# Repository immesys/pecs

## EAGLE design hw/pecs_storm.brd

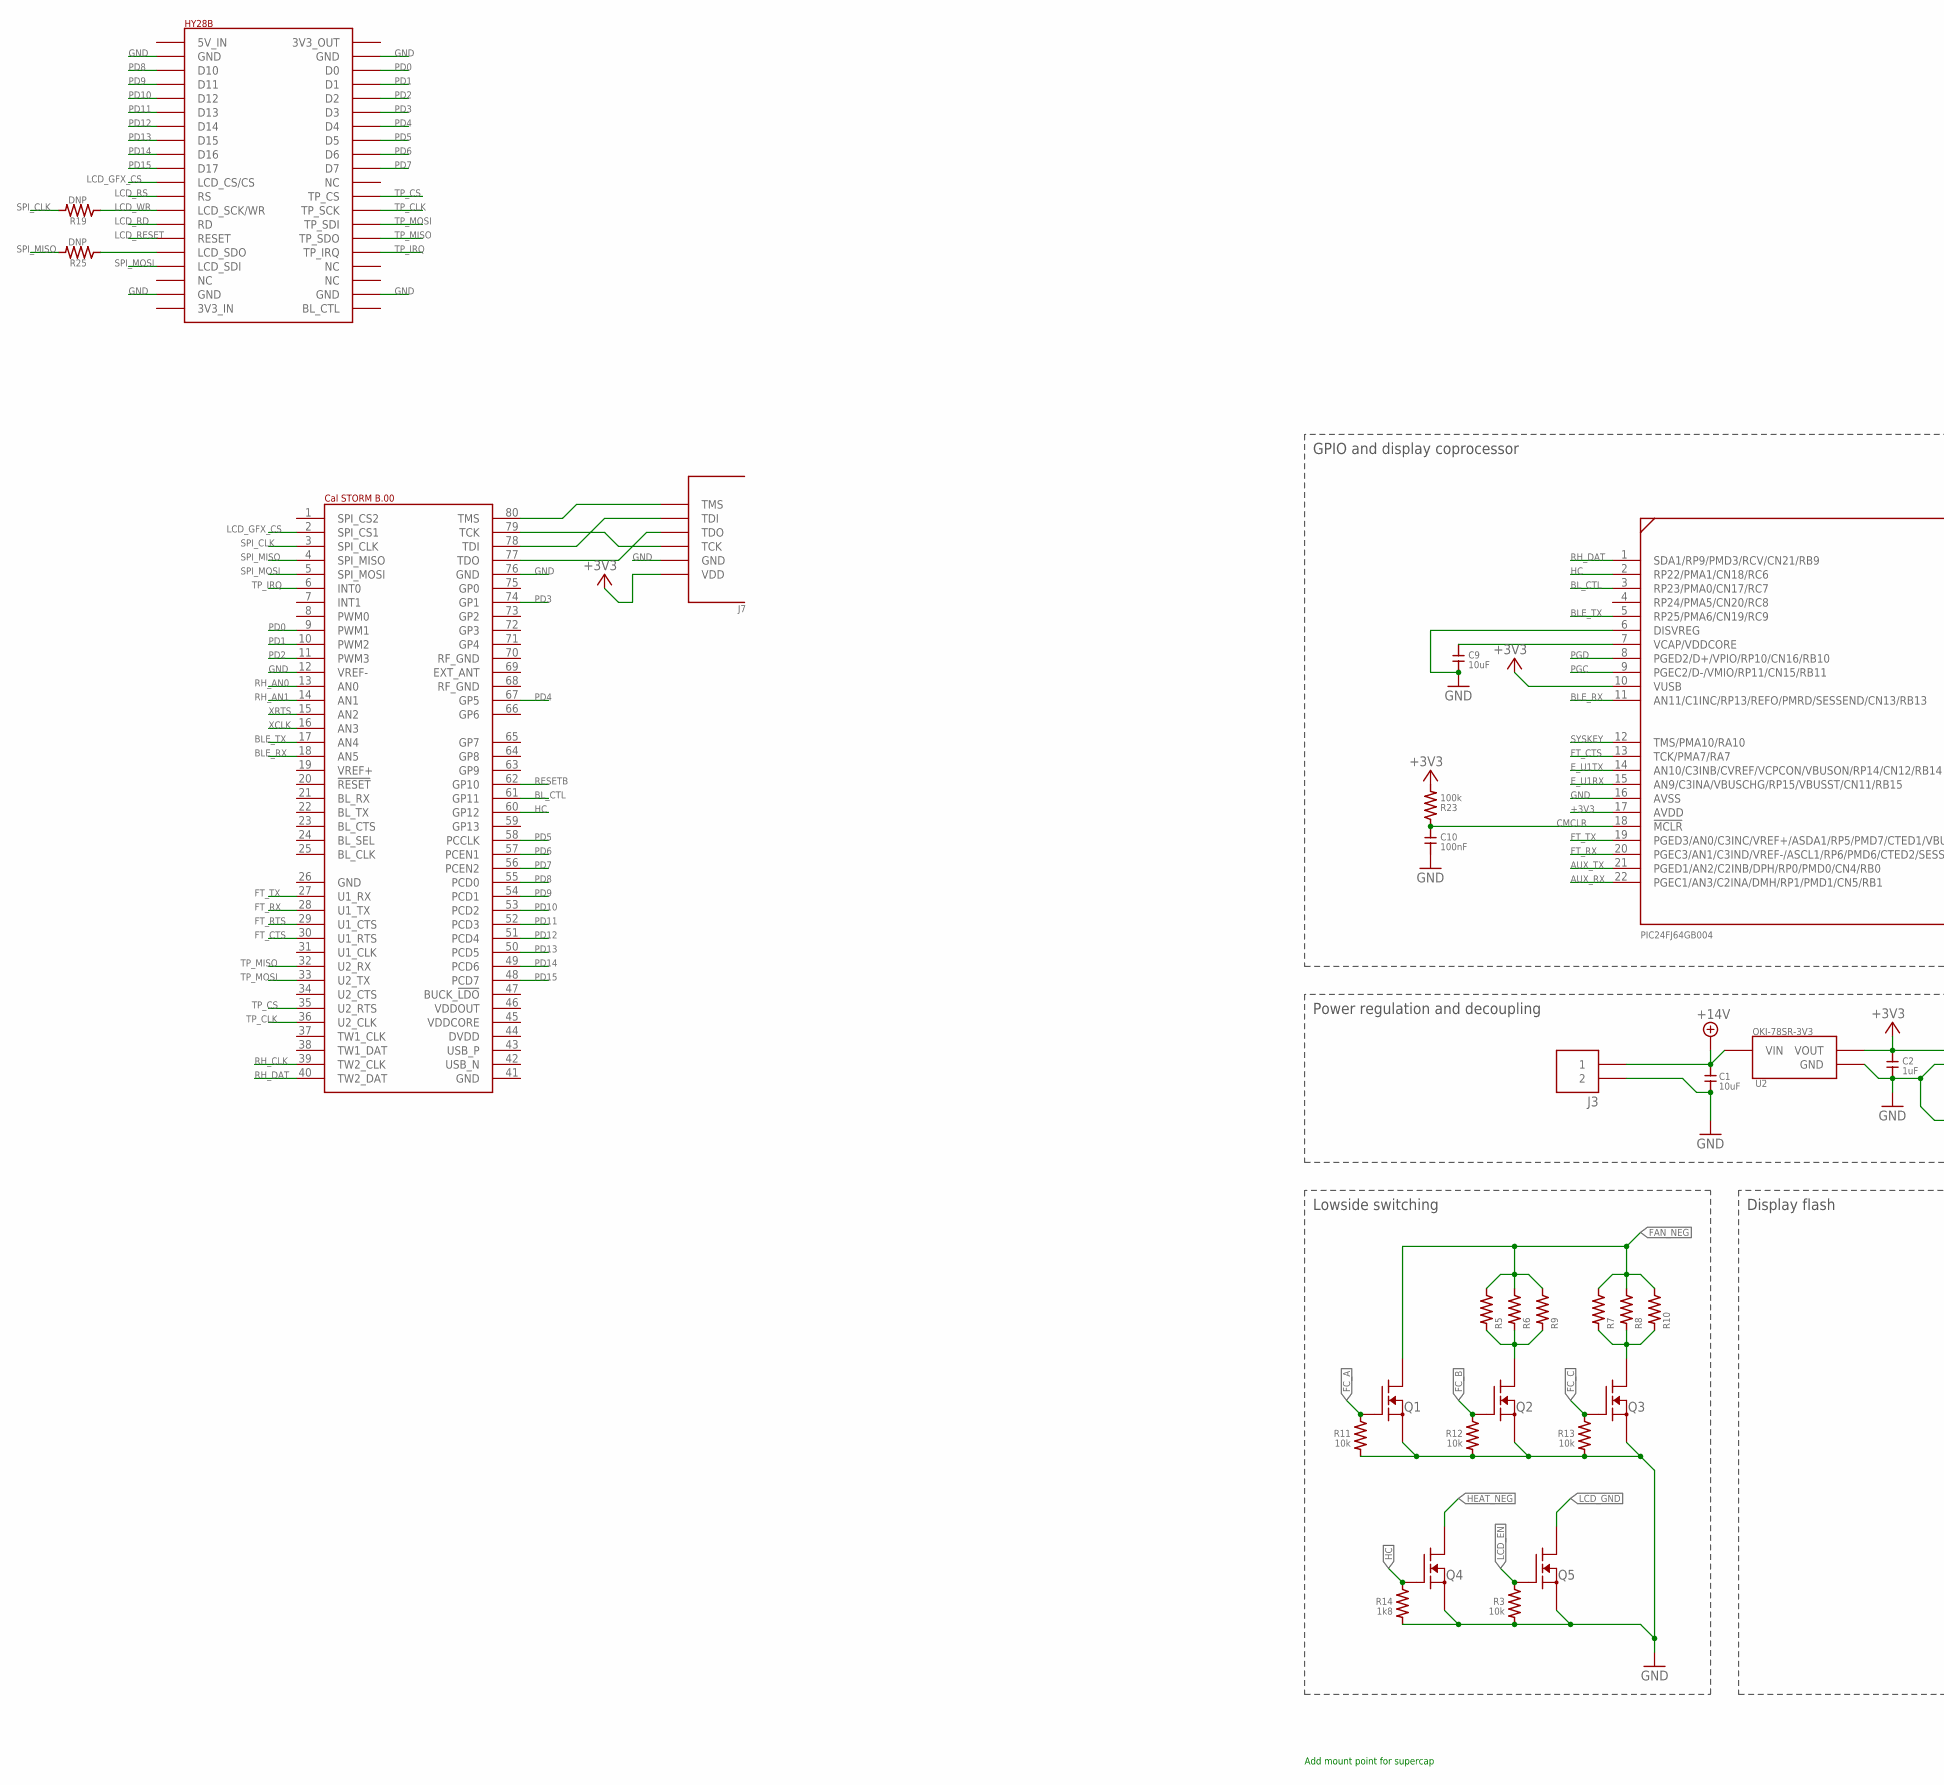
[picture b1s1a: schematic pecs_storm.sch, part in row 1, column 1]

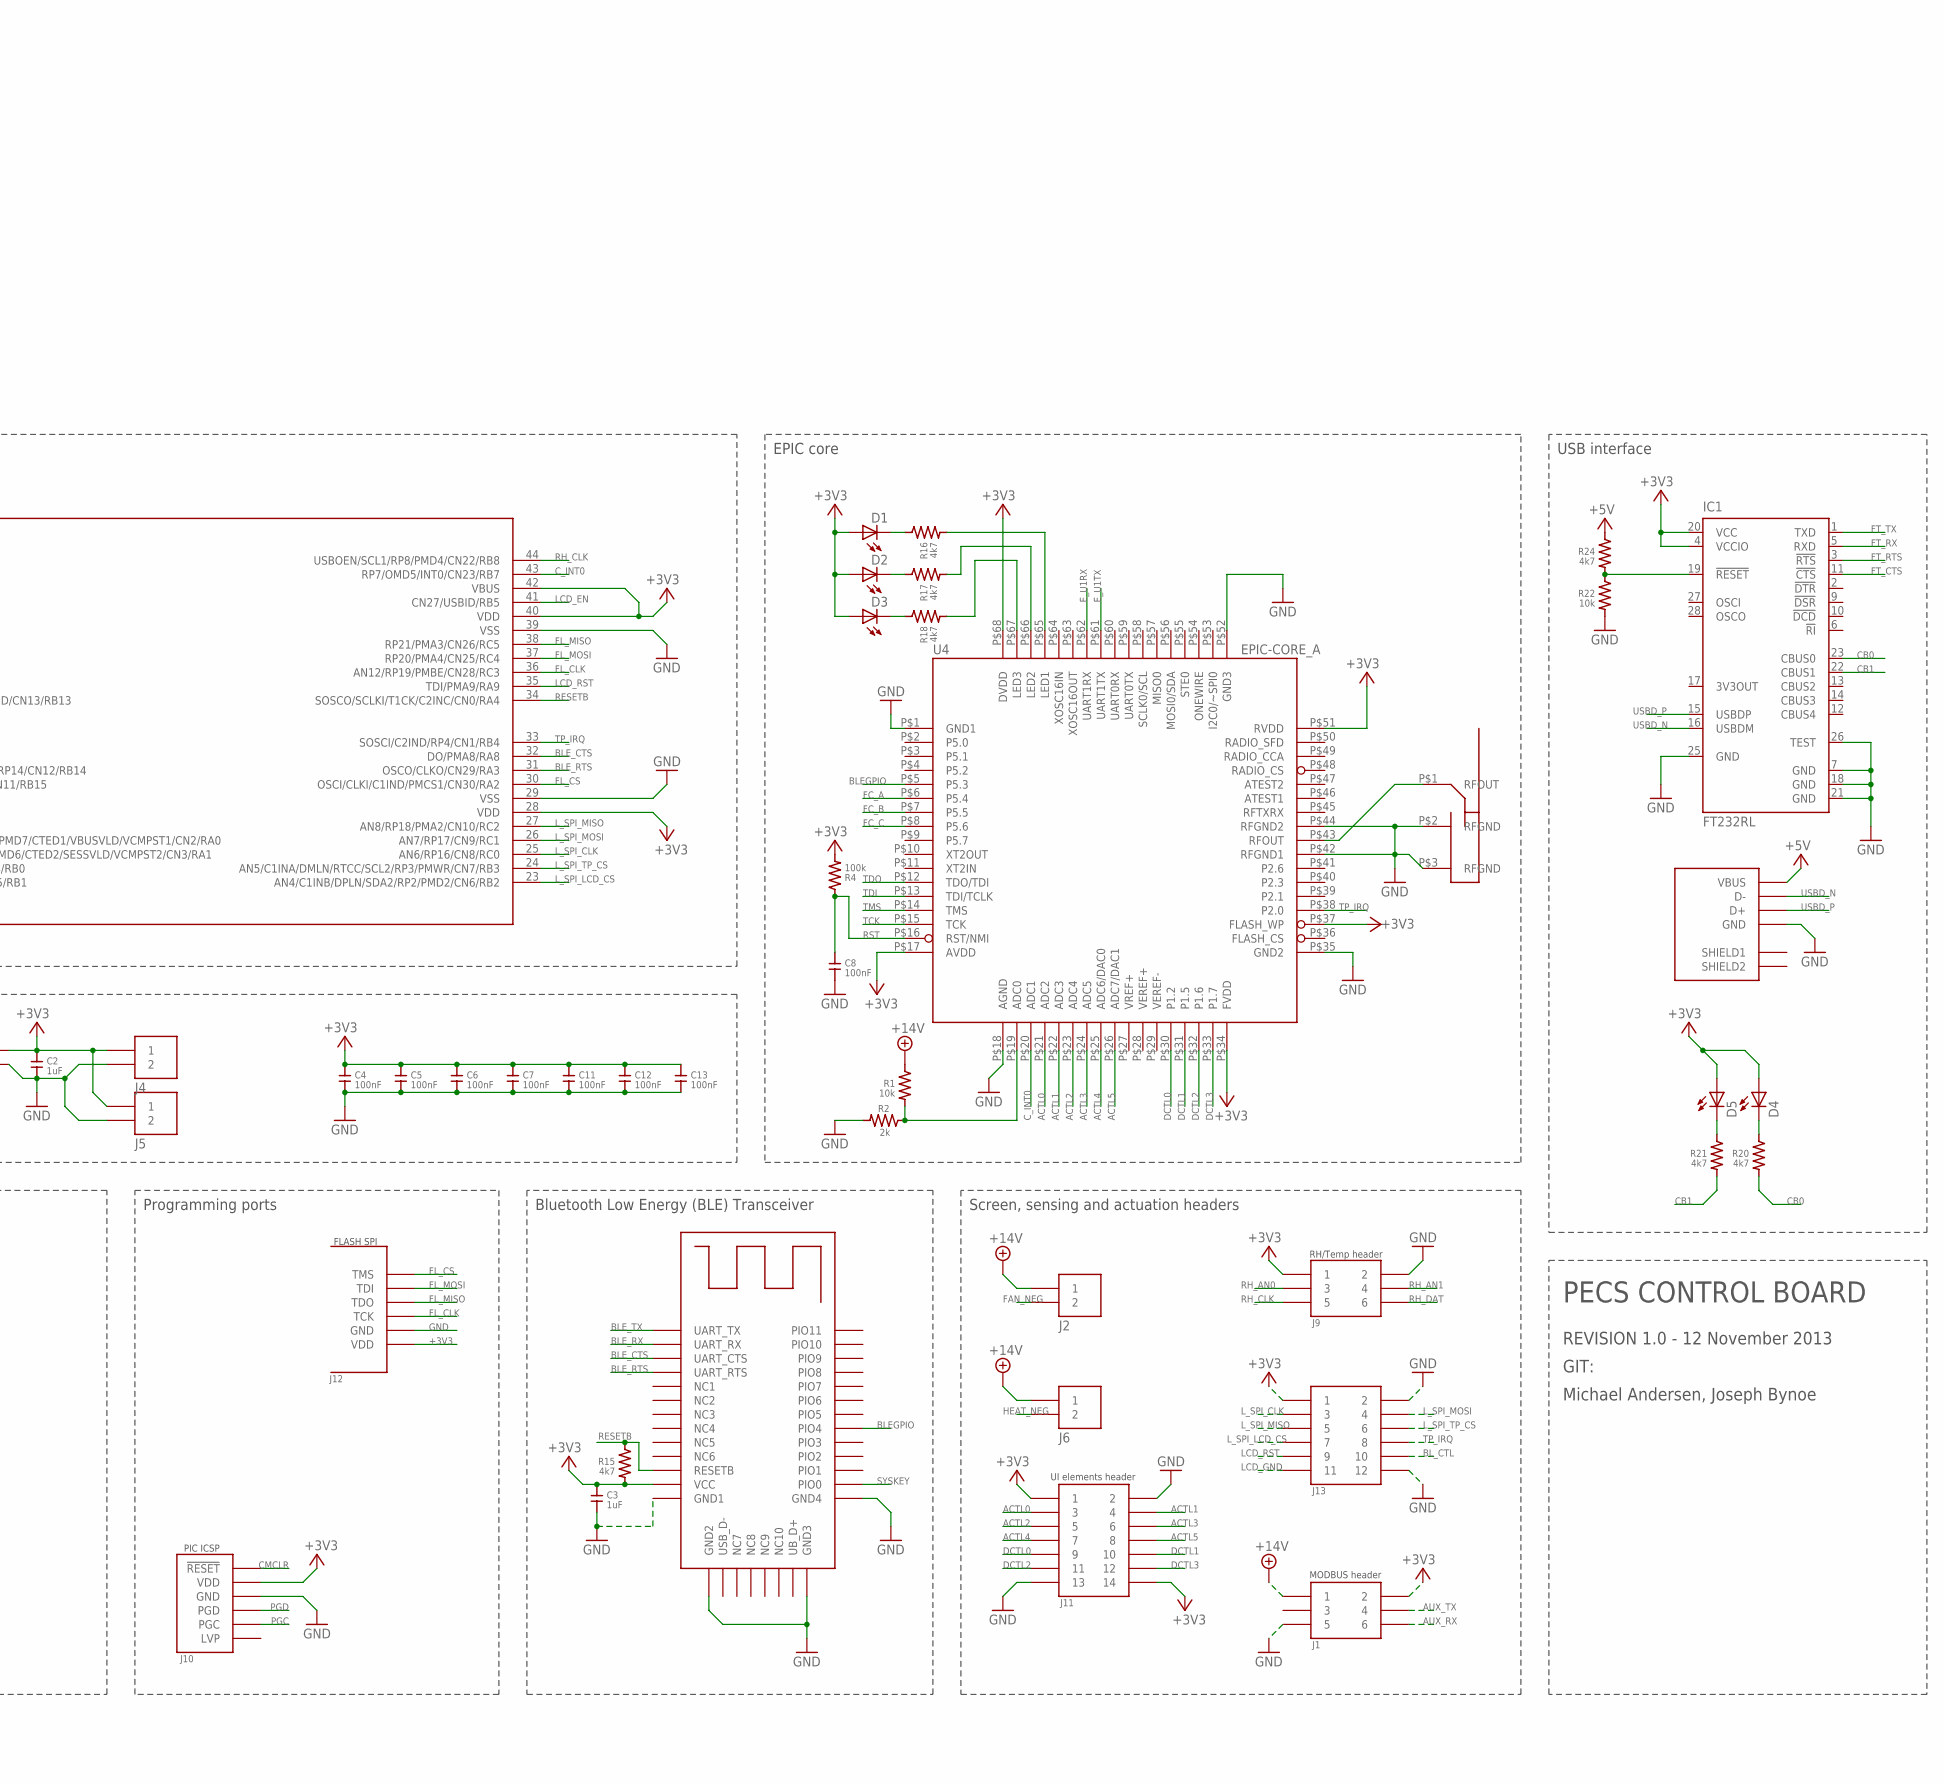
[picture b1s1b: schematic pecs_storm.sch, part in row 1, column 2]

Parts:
ANT1: PIFA-2.4GHZ
BLE1: HM10_BLE; HM10
C1, C9: 10uF; 0805
C2, C3: 1uF; 0805
C4, C5, C6, C7, C8, C10, C11, C12, C13: 100nF; 0805
D1, D2, D3, D4, D5: LED1206; LED-1206
IC1: FT232RL; SSOP28
J1, J9: HD.1-6
J2, J3, J4, J5, J6: H.1-2
J7, J12: JTAG
J10: ICSP_HDR; H.1-6
J11: HD.1-14; HD.1-16
J13: HD.1-12
Q1, Q2, Q3, Q4, Q5: NFET_DPAK; DPAK
R1, R3, R11, R12, R13, R22: 10k; 0805
R2: 2k; 0805
R4, R23: 100k; 0805
R5, R6, R7, R8, R9, R10: 1206_RESISTOR; 1206
R14: 1k8; 0805
R15, R16, R17, R18, R20, R21, R24: 4k7; 0805
R19, R25: DNP; 0805
U1: PIC24FJ32GB004; TQFP44
U2: OKI-78SR_3V3_SMPS; SMPS_MODULE
U3: HY28B; SCREEN
U4: EPIC-CORE_A; EPIC-LCC68
U5: STORM_B.00; STORM_LANDING
U$1: USB_B; USB_MOLEX_7041

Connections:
+3V3: BLE1.P$12 (VCC), C2.2, C3.2, C4.2, C5.2, C6.2, C7.2, C11.2, C12.2, C13.2, D1.A, D2.A, D3.A, D4.A, D5.A, IC1.4 (VCCIO), IC1.20 (VCC), J1.P2 (2), J4.P1 (1), J5.P1 (1), J7.VDD, J9.P1 (1), J10.P2 (VDD), J11.P1 (1), J11.P14 (14), J12.VDD, J13.P1 (1), R4.1, R15.1, R23.1, U1.10 (VUSB), U1.17 (AVDD), U1.28 (VDD), U1.40 (VDD), U1.42 (VBUS), U2.VOUT, U4.P$17 (AVDD), U4.P$34 (FVDD), U4.P$37 (FLASH_WP), U4.P$51 (RVDD), U4.P$68 (DVDD)
+5V: R24.2, U$1.1_VBUS (VBUS)
+14V: C1.2, J1.P1 (1), J2.P1 (1), J3.P1 (1), J6.P1 (1), R1.2, U2.VIN
ACTL0: J11.P3 (3), U4.P$21 (ADC2)
ACTL1: J11.P4 (4), U4.P$22 (ADC3)
ACTL2: J11.P5 (5), U4.P$23 (ADC4)
ACTL3: J11.P6 (6), U4.P$24 (ADC5)
ACTL4: J11.P7 (7), U4.P$25 (ADC6/DAC0)
ACTL5: J11.P8 (8), U4.P$26 (ADC7/DAC1)
AUX_RX: J1.P6 (6), U1.22 (PGEC1/AN3/C2INA/DMH/RP1/PMD1/CN5/RB1)
AUX_TX: J1.P4 (4), U1.21 (PGED1/AN2/C2INB/DPH/RP0/PMD0/CN4/RB0)
BLEGPIO: BLE1.P$27 (PIO4), U4.P$5 (P5.3)
BLE_CTS: BLE1.P$3 (UART_CTS), U1.32 (DO/PMA8/RA8)
BLE_RTS: BLE1.P$4 (UART_RTS), U1.31 (OSCO/CLKO/CN29/RA3)
BLE_RX: BLE1.P$2 (UART_RX), U1.11 (AN11/C1INC/RP13/REFO/PMRD/SESSEND/CN13/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), U5.18 (AN5)
BLE_TX: BLE1.P$1 (UART_TX), U1.5 (RP25/PMA6/CN19/RC9), U5.17 (AN4)
BL_CTL: J13.P10 (10), U1.3 (RP23/PMA0/CN17/RC7), U5.61 (GP11)
CB0: IC1.23 (CBUS0), R20.1
CB1: IC1.22 (CBUS1), R21.1
CMCLR: C10.2, J10.P1 (!RESET!), R23.2, U1.18 (!MCLR!)
C_INT0: U1.43 (RP7/OMD5/INT0/CN23/RB7), U4.P$20 (ADC1)
DCTL0: J11.P9 (9), U4.P$30 (P1.2)
DCTL1: J11.P10 (10), U4.P$31 (P1.5)
DCTL2: J11.P11 (11), U4.P$32 (P1.6)
DCTL3: J11.P12 (12), U4.P$33 (P1.7)
E_U1RX: U1.15 (AN9/C3INA/VBUSCHG/RP15/VBUSST/CN11/RB15), U4.P$62 (UART1RX)
E_U1TX: U1.14 (AN10/C3INB/CVREF/VCPCON/VBUSON/RP14/CN1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), U4.P$61 (UART1TX)
FAN_NEG: J2.P2 (2), Q1.TAG (D), R5.2, R6.2, R7.2, R8.2, R9.2, R10.2
FC_A: Q1.P1 (G), R11.2, U4.P$6 (P5.4)
FC_B: Q2.P1 (G), R12.2, U4.P$7 (P5.5)
FC_C: Q3.P1 (G), R13.2, U4.P$8 (P5.6)
FL_CLK: J12.TCK, U1.36 (AN12/RP19/PMBE/CN28/RC3)
FL_CS: J12.TMS, U1.30 (OSCI/CLKI/C1IND/PMCS1/CN30/RA2)
FL_MISO: J12.TDO, U1.38 (RP21/PMA3/CN26/RC5)
FL_MOSI: J12.TDI, U1.37 (RP20/PMA4/CN25/RC4)
FT_CTS: IC1.11 (!CTS), U1.13 (TCK/PMA7/RA7), U5.30 (U1_RTS)
FT_RTS: IC1.3 (!RTS), U5.29 (U1_CTS)
FT_RX: IC1.5 (RXD), U1.20 (PGEC3/AN1/C3IND/VREF-/ASCL1/RP6/PMD6/CT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), U5.28 (U1_TX)
FT_TX: IC1.1 (TXD), U1.19 (PGED3/AN0/C3INC/VREF+/ASDA1/RP5/PMD7/CT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), U5.27 (U1_RX)
GND: ANT1.P$2 (RFGND), ANT1.P$3 (RFGND), BLE1.P$13 (GND1), BLE1.P$14 (GND2), BLE1.P$21 (GND3), BLE1.P$22 (GND4), C1.1, C2.1, C3.1, C4.1, C5.1, C6.1, C7.1, C8.1, C9.1, C10.1, C11.1, C12.1, C13.1, IC1.7 (GND), IC1.18 (GND), IC1.21 (GND), IC1.25 (GND), IC1.26 (TEST), J1.P5 (5), J3.P2 (2), J4.P2 (2), J5.P2 (2), J7.GND, J9.P2 (2), J10.P3 (GND), J11.P2 (2), J11.P13 (13), J12.GND, J13.P2 (2), J13.P12 (12), Q1.P3 (S), Q2.P3 (S), Q3.P3 (S), Q4.P3 (S), Q5.P3 (S), R2.1, R3.1, R11.1, R12.1, R13.1, R14.1, R22.1, U1.6 (DISVREG), U1.16 (AVSS), U1.29 (VSS), U1.39 (VSS), U2.GND, U3.P$2 (GND), U3.P$19 (GND), U3.P$22 (GND), U3.P$39 (GND), U4.P$1 (GND1), U4.P$18 (AGND), U4.P$35 (GND2), U4.P$42 (RFGND1), U4.P$44 (RFGND2), U4.P$52 (GND3), U5.12 (VREF-), U5.76 (GND), U$1.4_GND (GND)
HC: Q4.P1 (G), R14.2, U1.2 (RP22/PMA1/CN18/RC6), U5.60 (GP12)
HEAT_NEG: J6.P2 (2), Q4.TAG (D)
LCD_EN: Q5.P1 (G), R3.2, U1.41 (CN27/USBID/RB5)
LCD_GFX_CS: U3.P$11 (LCD_CS/CS), U5.2 (SPI_CS1)
LCD_GND: J13.P11 (11), Q5.TAG (D)
LCD_RD: U3.P$14 (RD)
LCD_RESET: U3.P$15 (RESET)
LCD_RS: U3.P$12 (RS)
LCD_RST: J13.P9 (9), U1.35 (TDI/PMA9/RA9)
LCD_WR: R19.2, U3.P$13 (LCD_SCK/WR)
L_SPI_CLK: J13.P3 (3), U1.25 (AN6/RP16/CN8/RC0)
L_SPI_LCD_CS: J13.P7 (7), U1.23 (AN4/C1INB/DPLN/SDA2/RP2/PMD2/CN6/RB2)
L_SPI_MISO: J13.P5 (5), U1.27 (AN8/RP18/PMA2/CN10/RC2)
L_SPI_MOSI: J13.P4 (4), U1.26 (AN7/RP17/CN9/RC1)
L_SPI_TP_CS: J13.P6 (6), U1.24 (AN5/C1INA/DMLN/RTCC/SCL2/RP3/PMWR/CN7/R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)
unnamed: C9.2, U1.7 (VCAP/VDDCORE)
unnamed: R25.2, U3.P$16 (LCD_SDO)
unnamed: ANT1.P$1 (RFOUT), U4.P$43 (RFOUT)
unnamed: J7.TMS, U5.80 (TMS)
unnamed: J7.TCK, U5.79 (TCK)
unnamed: Q2.TAG (D), R5.1, R6.1, R9.1
unnamed: Q3.TAG (D), R7.1, R8.1, R10.1
unnamed: J7.TDI, U5.78 (TDI)
unnamed: D4.C, R20.2
unnamed: D1.C, R16.2
unnamed: D2.C, R17.2
unnamed: D3.C, R18.2
unnamed: R16.1, U4.P$65 (LED1)
unnamed: D5.C, R21.2
unnamed: R17.1, U4.P$66 (LED2)
unnamed: R18.1, U4.P$67 (LED3)
unnamed: J7.TDO, U5.77 (TDO)
unnamed: IC1.19 (!RESET), R22.2, R24.1
unnamed: R1.1, R2.2, U4.P$19 (ADC0)
PD0: U3.P$38 (D0), U5.9 (PWM1)
PD1: U3.P$37 (D1), U5.10 (PWM2)
PD2: U3.P$36 (D2), U5.11 (PWM3)
PD3: U3.P$35 (D3), U5.74 (GP1)
PD4: U3.P$34 (D4), U5.67 (GP5)
PD5: U3.P$33 (D5), U5.58 (PCCLK)
PD6: U3.P$32 (D6), U5.57 (PCEN1)
PD7: U3.P$31 (D7), U5.56 (PCEN2)
PD8: U3.P$3 (D10), U5.55 (PCD0)
PD9: U3.P$4 (D11), U5.54 (PCD1)
PD10: U3.P$5 (D12), U5.53 (PCD2)
PD11: U3.P$6 (D13), U5.52 (PCD3)
PD12: U3.P$7 (D14), U5.51 (PCD4)
PD13: U3.P$8 (D15), U5.50 (PCD5)
PD14: U3.P$9 (D16), U5.49 (PCD6)
PD15: U3.P$10 (D17), U5.48 (PCD7)
PGC: J10.P5 (PGC), U1.9 (PGEC2/D-/VMIO/RP11/CN15/RB11)
PGD: J10.P4 (PGD), U1.8 (PGED2/D+/VPIO/RP10/CN16/RB10)
RESETB: BLE1.P$11 (RESETB), R15.2, U1.34 (SOSCO/SCLKI/T1CK/C2INC/CN0/RA4), U5.62 (GP10)
RH_AN0: J9.P3 (3), U5.13 (AN0)
RH_AN1: J9.P4 (4), U5.14 (AN1)
RH_CLK: J9.P5 (5), U1.44 (USBOEN/SCL1/RP8/PMD4/CN22/RB8), U5.39 (TW2_CLK)
RH_DAT: J9.P6 (6), U1.1 (SDA1/RP9/PMD3/RCV/CN21/RB9), U5.40 (TW2_DAT)
RST: C8.2, R4.2, U4.P$16 (RST/NMI)
SPI_CLK: R19.1, U5.3 (SPI_CLK)
SPI_MISO: R25.1, U5.4 (SPI_MISO)
SPI_MOSI: U3.P$17 (LCD_SDI), U5.5 (SPI_MOSI)
SYSKEY: BLE1.P$23 (PIO0), U1.12 (TMS/PMA10/RA10)
TCK: U4.P$15 (TCK)
TDI: U4.P$13 (TDI/TCLK)
TDO: U4.P$12 (TDO/TDI)
TMS: U4.P$14 (TMS)
TP_CLK: U3.P$28 (TP_SCK), U5.36 (U2_CLK)
TP_CS: U3.P$29 (TP_CS), U5.35 (U2_RTS)
TP_IRQ: J13.P8 (8), U1.33 (SOSCI/C2IND/RP4/CN1/RB4), U3.P$25 (TP_IRQ), U4.P$38 (P2.0), U5.6 (INT0)
TP_MISO: U3.P$26 (TP_SDO), U5.32 (U2_RX)
TP_MOSI: U3.P$27 (TP_SDI), U5.33 (U2_TX)
USBD_N: IC1.16 (USBDM), U$1.2_D- (D-)
USBD_P: IC1.15 (USBDP), U$1.3_D+ (D+)
XCLK: U5.16 (AN3)
XRTS: U5.15 (AN2)

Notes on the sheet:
PIC24FJ64GB004
FLASH SPI
Bluetooth Low Energy (BLE) Transceiver
Programming ports
PIC ICSP
Screen, sensing and actuation headers
RH/Temp header
UI elements header
MODBUS header
Lowside switching
GPIO and display coprocessor
Power regulation and decoupling
EPIC core
Display flash
USB interface
PECS CONTROL BOARD
REVISION 1.0 - 12 November 2013
GIT:
Michael Andersen, Joseph Bynoe
Add mount point for supercap

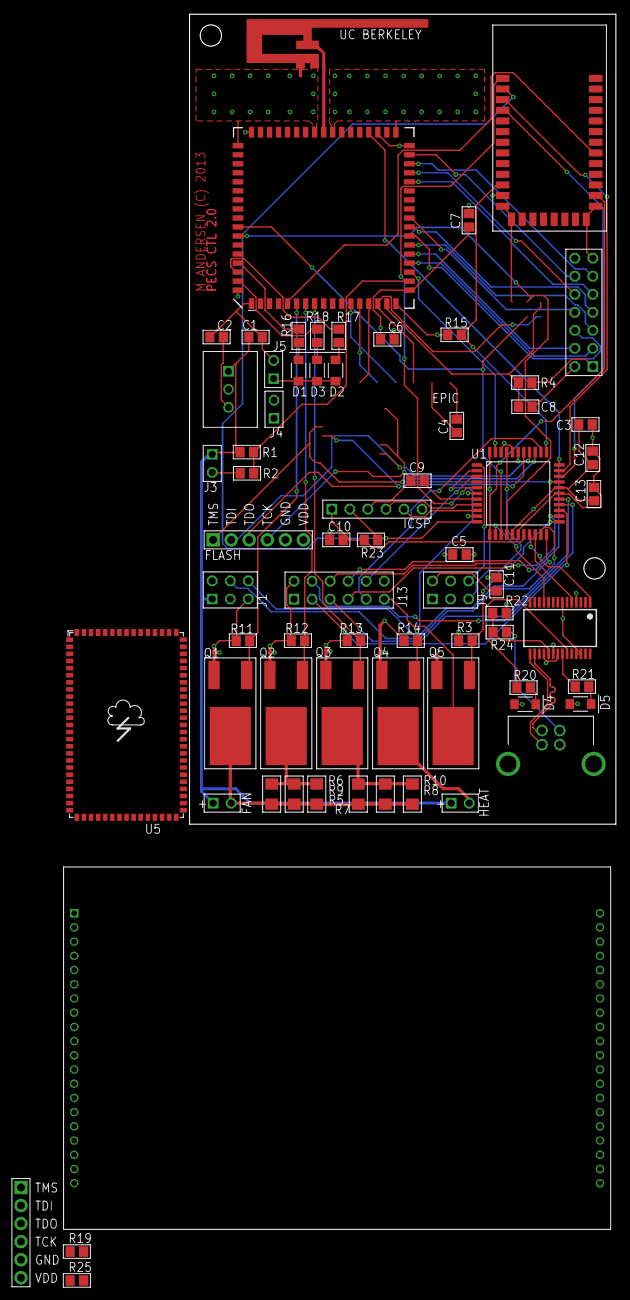
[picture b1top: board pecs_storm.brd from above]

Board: 4 copper layers, 60.0 x 114.0 mm, 69 parts (0 on the bottom side), 106 nets.

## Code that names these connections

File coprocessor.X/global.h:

/* 
 * File:   global.h
 * Author: immesys
 *
 * Created on November 23, 2013, 3:20 PM
 */

#ifndef GLOBAL_H
#define	GLOBAL_H

#include <xc.h>
#include <stdint.h>
#include "assets.h"


#define LCD_X  240
#define LCD_Y  320



inline void lcd_select(void);
inline void lcd_deselect(void);
inline void lcd_write_index(uint8_t idx);
inline void lcd_write_data_start(void);
inline void lcd_write_data_word(uint16_t w);
inline void lcd_write_data_body(uint16_t w);
inline void lcd_write_reg(uint16_t addr, uint16_t value);
inline uint16_t lcd_read_data(void);
inline uint16_t lcd_read_reg(uint16_t addr);
inline void lcd_set_cursor(uint16_t x, uint16_t y);
inline uint8_t spi2_rw_b(uint8_t b);
inline void flash_begin_read(uint32_t address);

typedef struct
{
    int32_t x;
    int32_t y;
} point_t;

/**
 * Delay in units of half a microsecond
 * @param x number of half microseconds to delay
 */
void delay_hus(uint16_t x);


/**
 * Delay for X milliseconds.
 * @param x the number of milliseconds to delay for
 */
void delay_ms(uint16_t x);


//config.c
void init_hw(void);

//uart.c
inline void uart1_wb(uint8_t v);
int write(int handle, void *buffer, unsigned int len);
inline void tc(uint16_t v);
inline void uart1_wb(uint8_t v);
void write_epic_command(uint8_t cmd, uint8_t val);

//spi.c
void delay_ms(uint16_t x);
void lcd_init(void);
inline void spi2_w_b_xdiscard(uint8_t b);
inline void spi2_w_b(uint8_t b);
inline void flash_select(void);
inline void flash_deselect(void);
inline void lcd_start_gfx();
inline void lcd_end_gfx();
uint8_t tp_sample_xy(uint16_t *x, uint16_t *y);
void tp_get_raw_xy(uint16_t *x, uint16_t *y);

//graphics.c
void blit_rect(uint16_t sx, uint16_t sy, uint16_t width, uint16_t height, uint32_t start_address);
inline void check_flash_window_blit();
inline void check_flash_full_blit();
inline void draw_calibrate_bg();
inline void erase_calibrate_point(uint16_t x, uint16_t y);
inline void draw_calibrate_point(uint16_t x, uint16_t y);
void blit_window(uint16_t img_sx, uint16_t img_sy, uint16_t width, uint16_t height,
                 uint16_t asset_sx, uint16_t asset_sy, uint16_t asset_width, uint16_t asset_height, uint32_t asset_address);
void draw_bar_screen_full();
inline void do_screen_touch(uint16_t x, uint16_t y);
void poll_tp();
void init_vals();
void poll_screen();
void tp_calibrate(void);
void gen_qr_code(const char* str);
void draw_qr_code();
inline void draw_pecs_bg();
void poll_val_uploads();
void unpack();
inline void uart2_wb(uint8_t v);
void rxipoll();
void draw_qr_hexcode();

// rht.c
uint16_t read_temp();
uint16_t read_rel_humidity();
void reset_rht();
void poll_temps();

//Logic
void set_occupancy(uint8_t is_occupied);
void set_heat(uint8_t val, uint8_t total, uint8_t source);
void set_fans(uint8_t val, uint8_t total, uint8_t origin);
void fanslider(uint8_t val, uint8_t total);
void heatslider(uint8_t val, uint8_t total);
void send_epic_packet(uint8_t cmd, uint8_t val);


typedef enum
{
    fs_idle,
    fs_full_blit,
    fs_window_blit,
    fs_overlay_blit
} flashstate_t;



//TODO double? Really?
typedef struct Matrix
{
   int32_t  An,
            Bn,
            Cn,
            Dn,
            En,
            Fn,
            Divider ;
} matrix_t ;

typedef union
{
    uint32_t u32;
    struct
    {
        uint16_t u16_low;
        uint16_t u16_high;
    };
} split_u32_t;

typedef enum {ss_unoccupied, ss_active_to_idle, ss_qr_to_idle, ss_idle, ss_qr_entry, ss_qr, ss_bar_entry, ss_bars} screen_state_t;

//Pins
#define LCD_TP_MOSI_RPO    _RP17R
#define LCD_TP_SCK_RPO     _RP16R

#define FL_MOSI_RPO     _RP20R
#define FL_SCK_RPO      _RP19R
#define TP_CS_RPO       _RP15R
#define TP_BL_CTL_RPO   _RP23R
#define HC_RPO          _RP22R

#define PIC_TO_EPIC_RPO  _RP15R
#define EPIC_TO_PIC_RPI  14

#define BLE_TX_RPI       25
#define BLE_RX_RPO      _RP13R

//#define DEBUG_RPO       _RP5R


#define LCD_MISO_RPI    18
#define FL_MISO_RPI     21

#define TP_IRQ          _RB4
#define TP_IRQ_TRIS     _TRISB4

#define FT_RX_RPO       _RP6R
#define FT_TX_RPI       5 //RP5 pin

#define LCD_RST_TRIS    _TRISA9
#define LCD_RST         _LATA9

#define LCD_SS_TRIS     _TRISB2
#define TP_SS_TRIS      _TRISB3
#define LCD_SS          _LATB2
#define TP_SS           _LATB3
#define LCD_EN_TRIS     _TRISB5
#define LCD_EN          _LATB5


//#define DBG2_TRIS       _TRISB5
//#define DBG2            _LATB5

#define FL_SS           _LATA2
#define FL_SS_TRIS      _TRISA2

#define LCD_BL          OC1R
#define HEAT            OC2R


#define BLUEBAR_POSITION_X 40
#define BLUEBAR_POSITION_Y 48
#define REDBAR_POSITION_X  40
#define REDBAR_POSITION_Y  142

#define BLUEBAR2_POSITION_X 31
#define BLUEBAR2_POSITION_Y 45
#define REDBAR2_POSITION_X  31
#define REDBAR2_POSITION_Y  139

#define V_OFFSET 22
#define OV_SENTINEL 0xF7
#define KNOB_START_X 38
#define BG_OVERFLOW 4
#define LCD_SPI_SPRESCALE 0b101 //0b101 3:1 == 5.3 Mhz
#define LCD_SPI_PPRESCALE 0b11  //0b11 = 1:1

#define TP_SPI_SPRESCALE  0b111 //0b111 1:1
#define TP_SPI_PPRESCALE  0b01  //0b01 16:1 == 1Mhz

/* AD channel selection command and register */
#define	TP_CHX 	0x90 	/* channel Y+ selection command */
#define	TP_CHY 	0xd0	/* channel X+ selection command*/

#define TP_POLL_THRESHOLD   100000 //50ms
#define TEMP_POLL_THRESHOLD 2000000L //1s
#define RED_TP_START_Y 142
#define RED_TP_END_Y   192


#define BLUE_TP_START_Y 48
#define BLUE_TP_END_Y   98
#define BOTH_TP_START_X 0
#define BOTH_TP_END_X   320

#define MAX_V           247

#define SOURCE_CLOUD 1
#define SOURCE_SCREEN 2



#endif	/* GLOBAL_H */

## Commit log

2013-10-19 Added some docs
2013-10-20 epic files
2013-10-29 Control board progress
2013-10-29 2 am on october 29
2013-11-13 Schematic nearly complete
2013-11-13 Version 2.0, gerbers rendered
2013-11-14 joe's v1
2013-11-20 PECS TOS APP, site
2013-11-20 Website according to joe
2013-11-20 Web Page after Mongodb :s
2013-11-20 Website updates 1:14AM
2013-11-20 MPA changes
2013-11-20 Website 1:32 Joe is a Champ
2013-11-20 Tabbed files
2013-11-20 Chair ID
2013-11-22 Changes on server
2013-11-24 Proof of concept coprocessor at correct frequency with debug uart
2013-11-24 Screen code
2013-11-28 Work on screen assets / flash programming scripts
2013-11-30 -O1 is breaking everything, as usual
2013-11-30 Got it to compile with -O1
2013-11-30 Trying to write two bytes at a time failed hard due to SRMPT bit weirdness
2013-11-30 Progress on screen rendering
2013-11-30 About to integrate touch
2013-12-01 Screen touch system working
2013-12-03 Web page updates
2013-12-03 Changes to the site
2013-12-03 Site hotfixes
2013-12-03 Init to current value
2013-12-04 joe's werk
2013-12-04 Joes Work 7pm
2013-12-04 Tweaked gitignore, error page and tos app
2013-12-04 Joe 2 files
2013-12-04 A BOOT
2013-12-04 I'm Commiting
2013-12-04 sum mary
2013-12-04 Pushhhhhhh
2013-12-04 Fix grammar
2013-12-04 Add favicons
2013-12-04 Resend if chair doesn't ack setting change
2013-12-04 Changed title
2013-12-04 hotfix
2013-12-06 TOS App, trying to rollback brd
2013-12-06 Add real coprocessor
2013-12-06 New Pictures for Home Page
2013-12-06 Working cloud -> chair
2013-12-06 Changes for measurement sources
2013-12-08 Coprocessor work
2013-12-09 Temp/RH sensor
2013-12-09 Changes to site
2013-12-09 Hotfixes
2013-12-09 Uploads of bars to cloud works
2013-12-09 Add site temperature
2013-12-09 Add site vars hook
2013-12-09 Auto update script
2013-12-10 Tweak slider updates
2013-12-12 Mad changes
2013-12-12 Try get site working
2013-12-22 End of semester code drop
2014-01-01 Working on new firmware version
2014-01-02 Screen letters resized
2014-02-13 Some old hotfixes

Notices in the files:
hw/pecs_storm.brd:
M ANDERSEN (C) 2013
